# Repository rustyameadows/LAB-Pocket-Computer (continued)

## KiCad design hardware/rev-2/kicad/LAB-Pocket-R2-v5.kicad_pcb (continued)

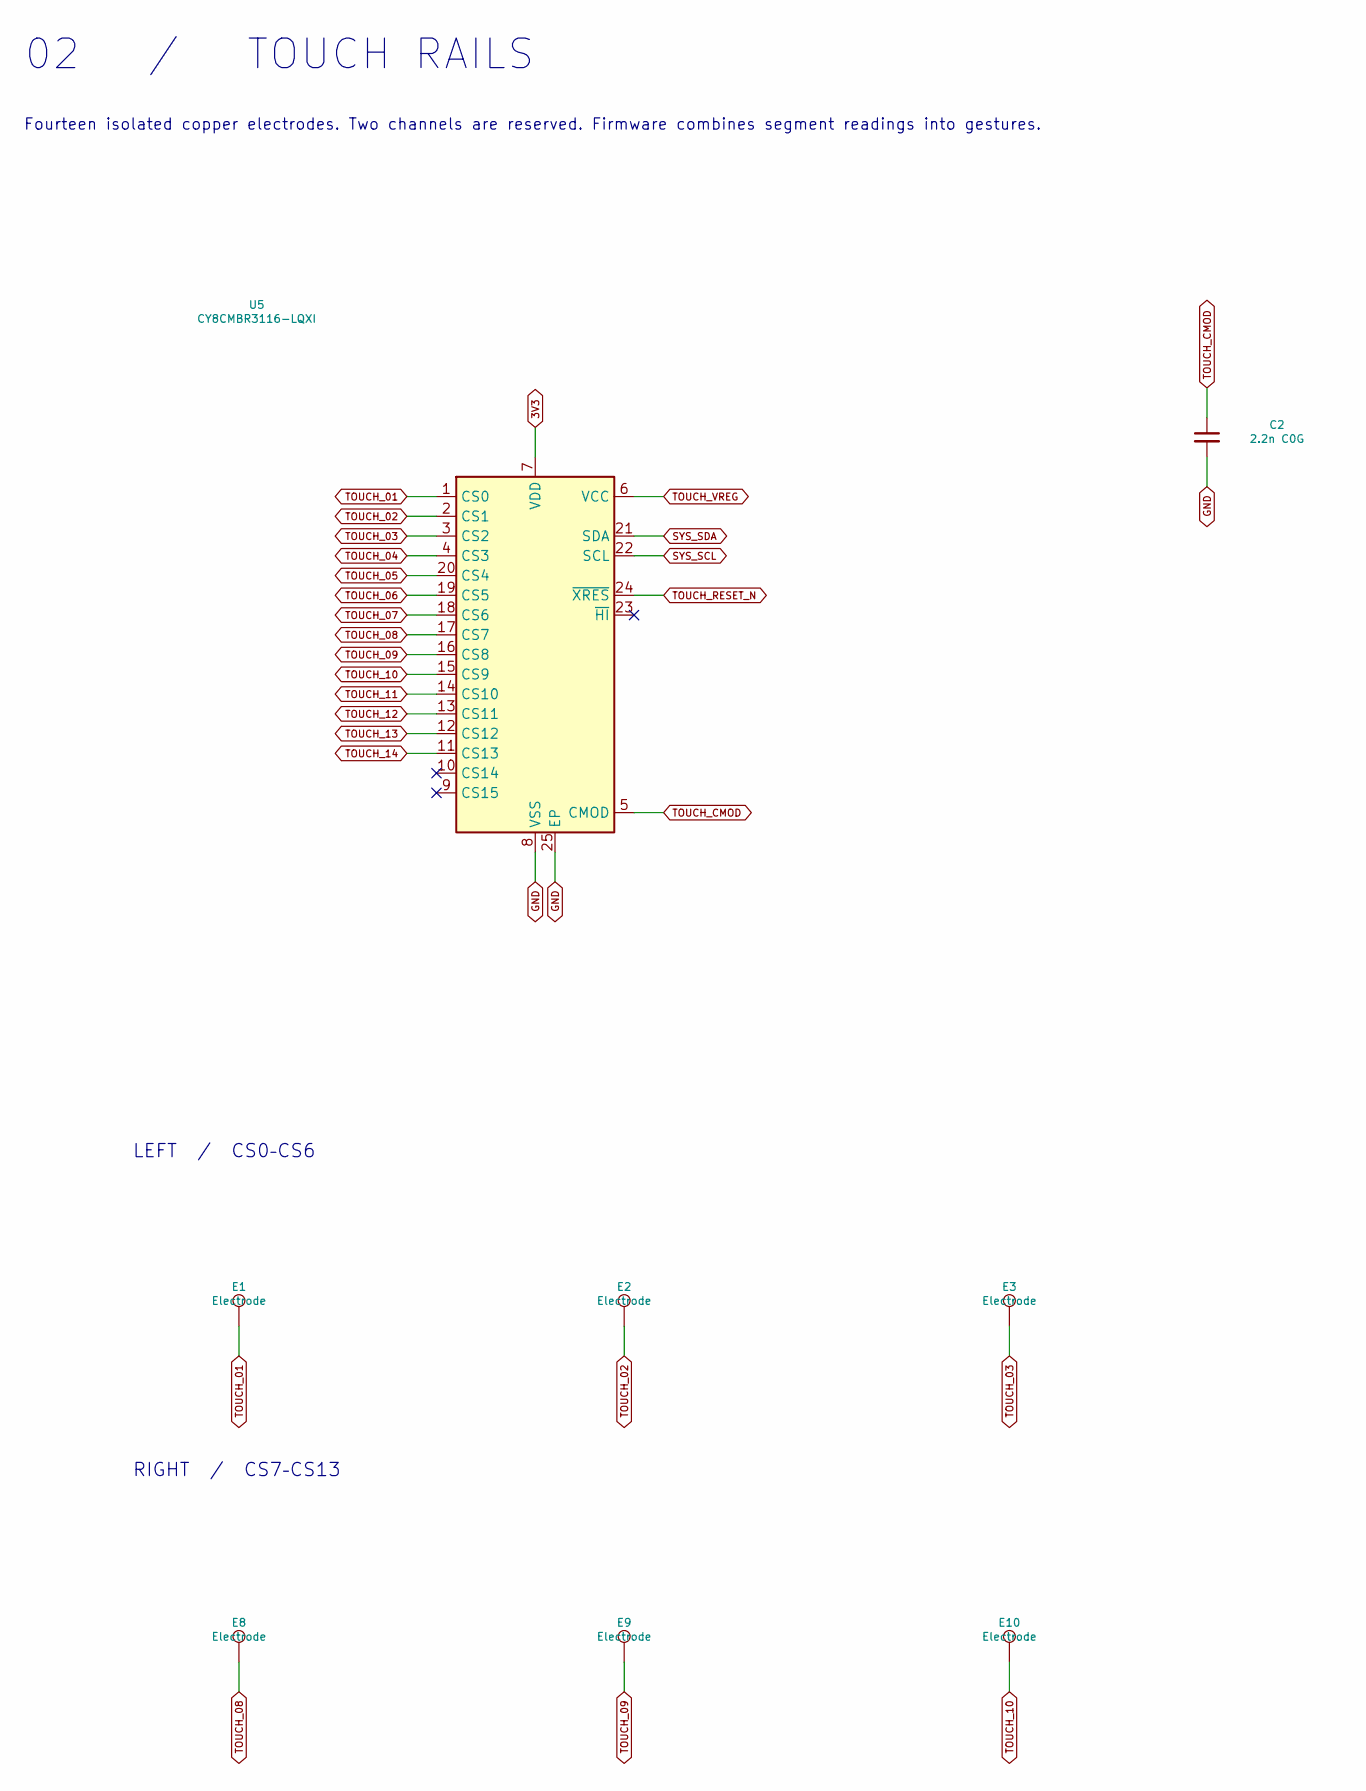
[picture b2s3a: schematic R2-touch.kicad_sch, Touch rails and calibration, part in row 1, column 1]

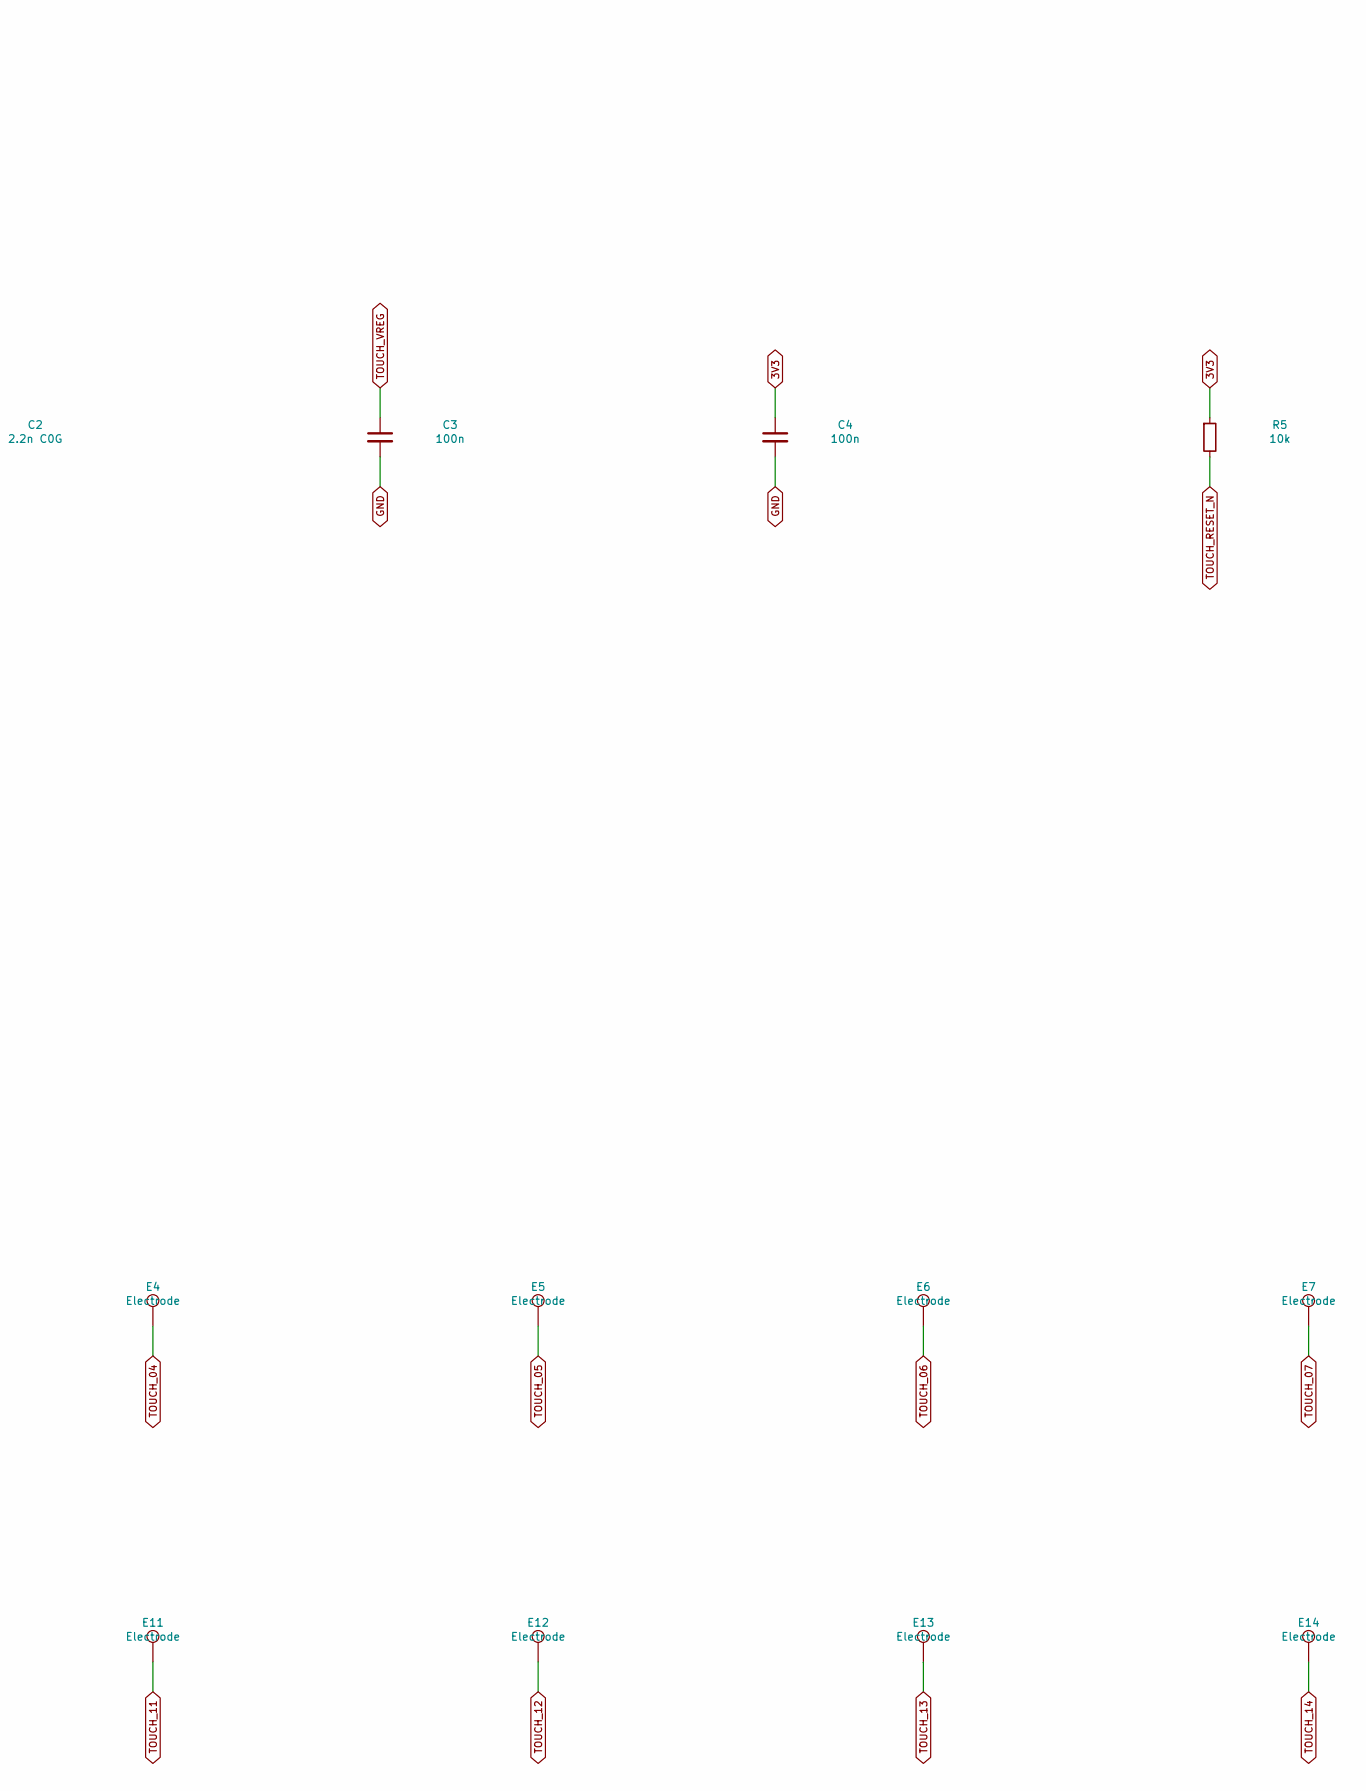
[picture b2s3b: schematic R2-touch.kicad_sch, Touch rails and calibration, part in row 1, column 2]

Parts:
C2: 2.2n C0G; C_0603_1608Metric; MPN C0603C222J5GACTU
C3, C4: 100n; C_0603_1608Metric; MPN C0603C104K5RACTU
E1, E2, E3, E4, E5, E6, E7, E8, E9, E10, E11, E12, E13, E14: Electrode; Touch_7.6x5.0; MPN PCB feature
R5: 10k; R_0603_1608Metric; MPN CRCW060310K0FKEA
U5: CY8CMBR3116-LQXI; QFN-24-1EP_4x4mm_P0.5mm_EP2.6x2.6mm; MPN CY8CMBR3116-LQXI

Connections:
3V3: C4.1, R5.1, U5.7 (VDD); also elsewhere on the board
GND: C2.2, C3.2, C4.2, U5.8 (VSS), U5.25 (EP); also elsewhere on the board
SYS_SCL: U5.22 (SCL); also elsewhere on the board
SYS_SDA: U5.21 (SDA); also elsewhere on the board
TOUCH_01: E1.1, U5.1 (CS0)
TOUCH_02: E2.1, U5.2 (CS1)
TOUCH_03: E3.1, U5.3 (CS2)
TOUCH_04: E4.1, U5.4 (CS3)
TOUCH_05: E5.1, U5.20 (CS4)
TOUCH_06: E6.1, U5.19 (CS5)
TOUCH_07: E7.1, U5.18 (CS6)
TOUCH_08: E8.1, U5.17 (CS7)
TOUCH_09: E9.1, U5.16 (CS8)
TOUCH_10: E10.1, U5.15 (CS9)
TOUCH_11: E11.1, U5.14 (CS10)
TOUCH_12: E12.1, U5.13 (CS11)
TOUCH_13: E13.1, U5.12 (CS12)
TOUCH_14: E14.1, U5.11 (CS13)
TOUCH_CMOD: C2.1, U5.5 (CMOD)
TOUCH_RESET_N: R5.2, U5.24 (~XRES)
TOUCH_VREG: C3.1, U5.6 (VCC)

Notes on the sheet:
02 / TOUCH RAILS
Fourteen isolated copper electrodes. Two channels are reserved. Firmware combines segment readings into gestures.
LEFT / CS0–CS6
RIGHT / CS7–CS13

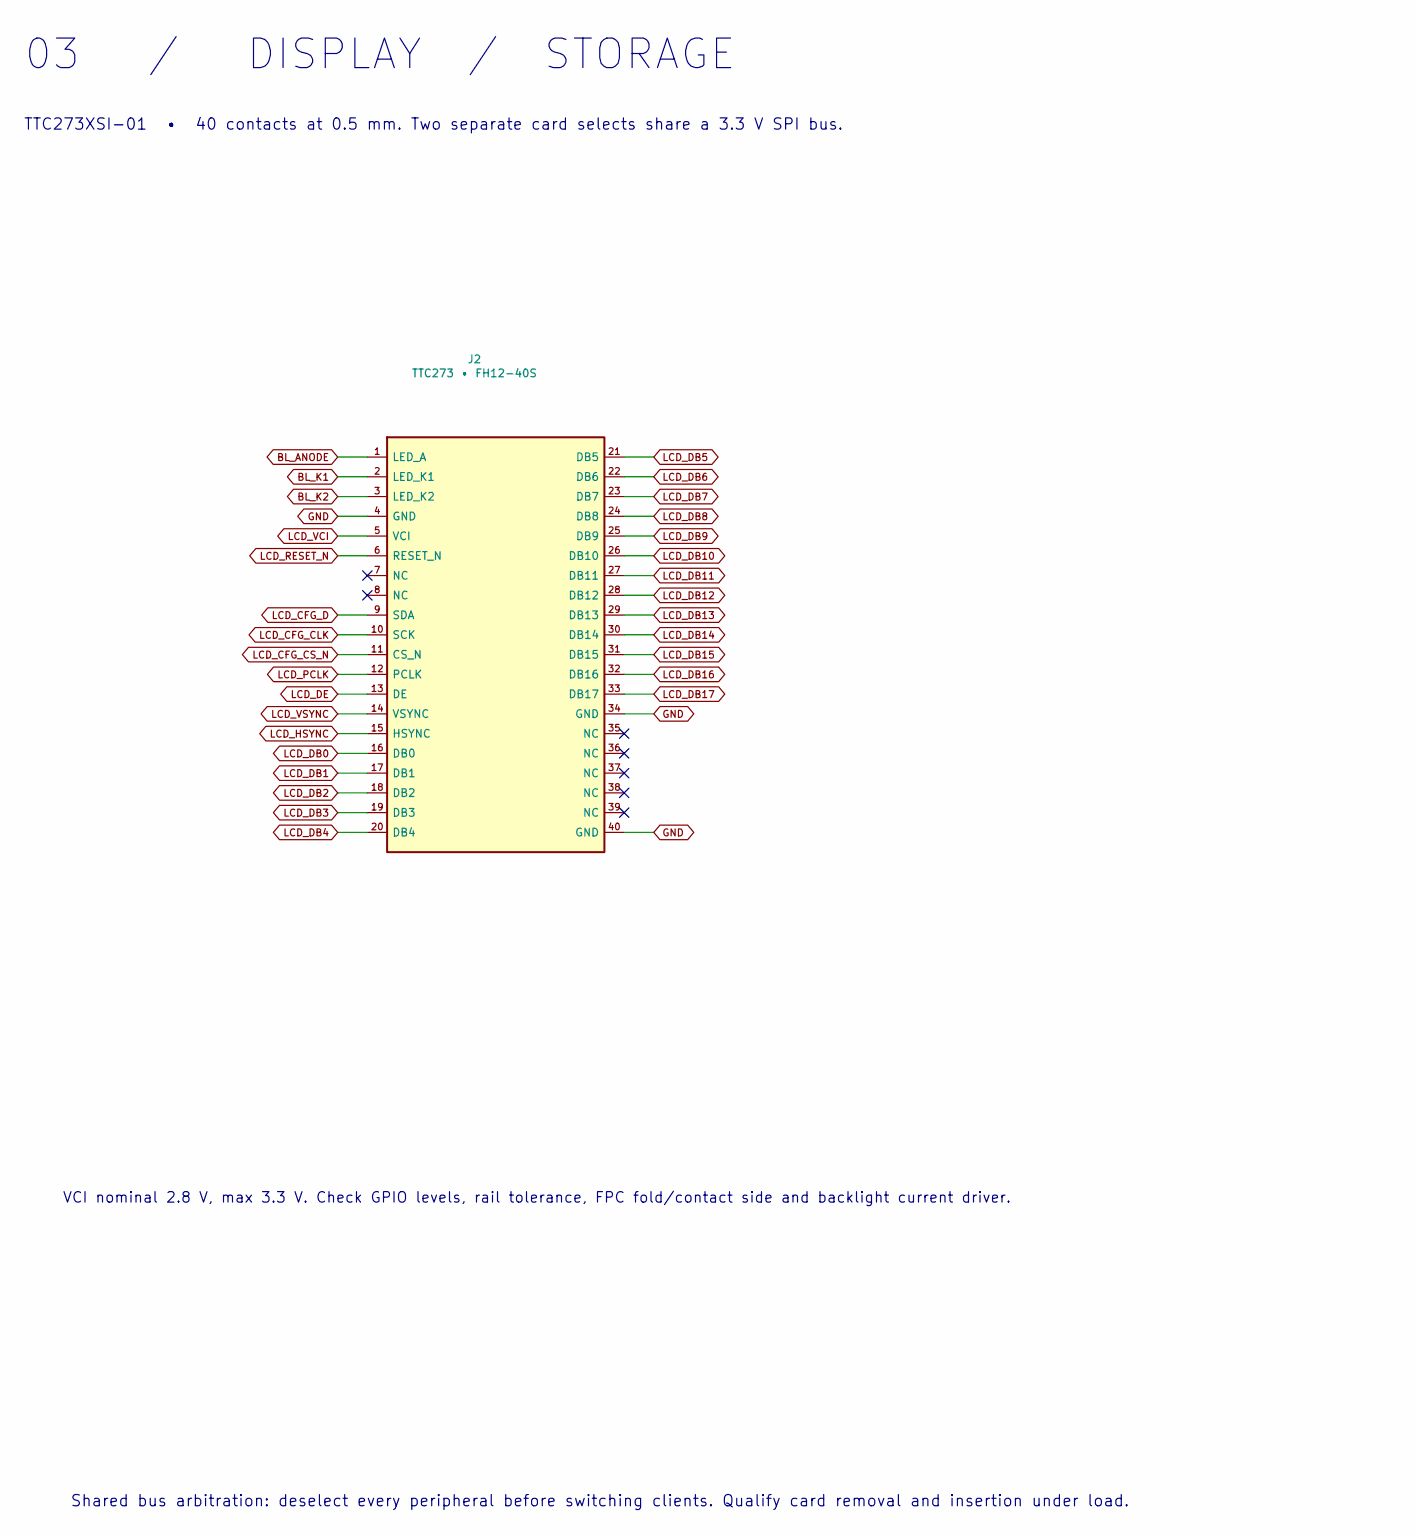
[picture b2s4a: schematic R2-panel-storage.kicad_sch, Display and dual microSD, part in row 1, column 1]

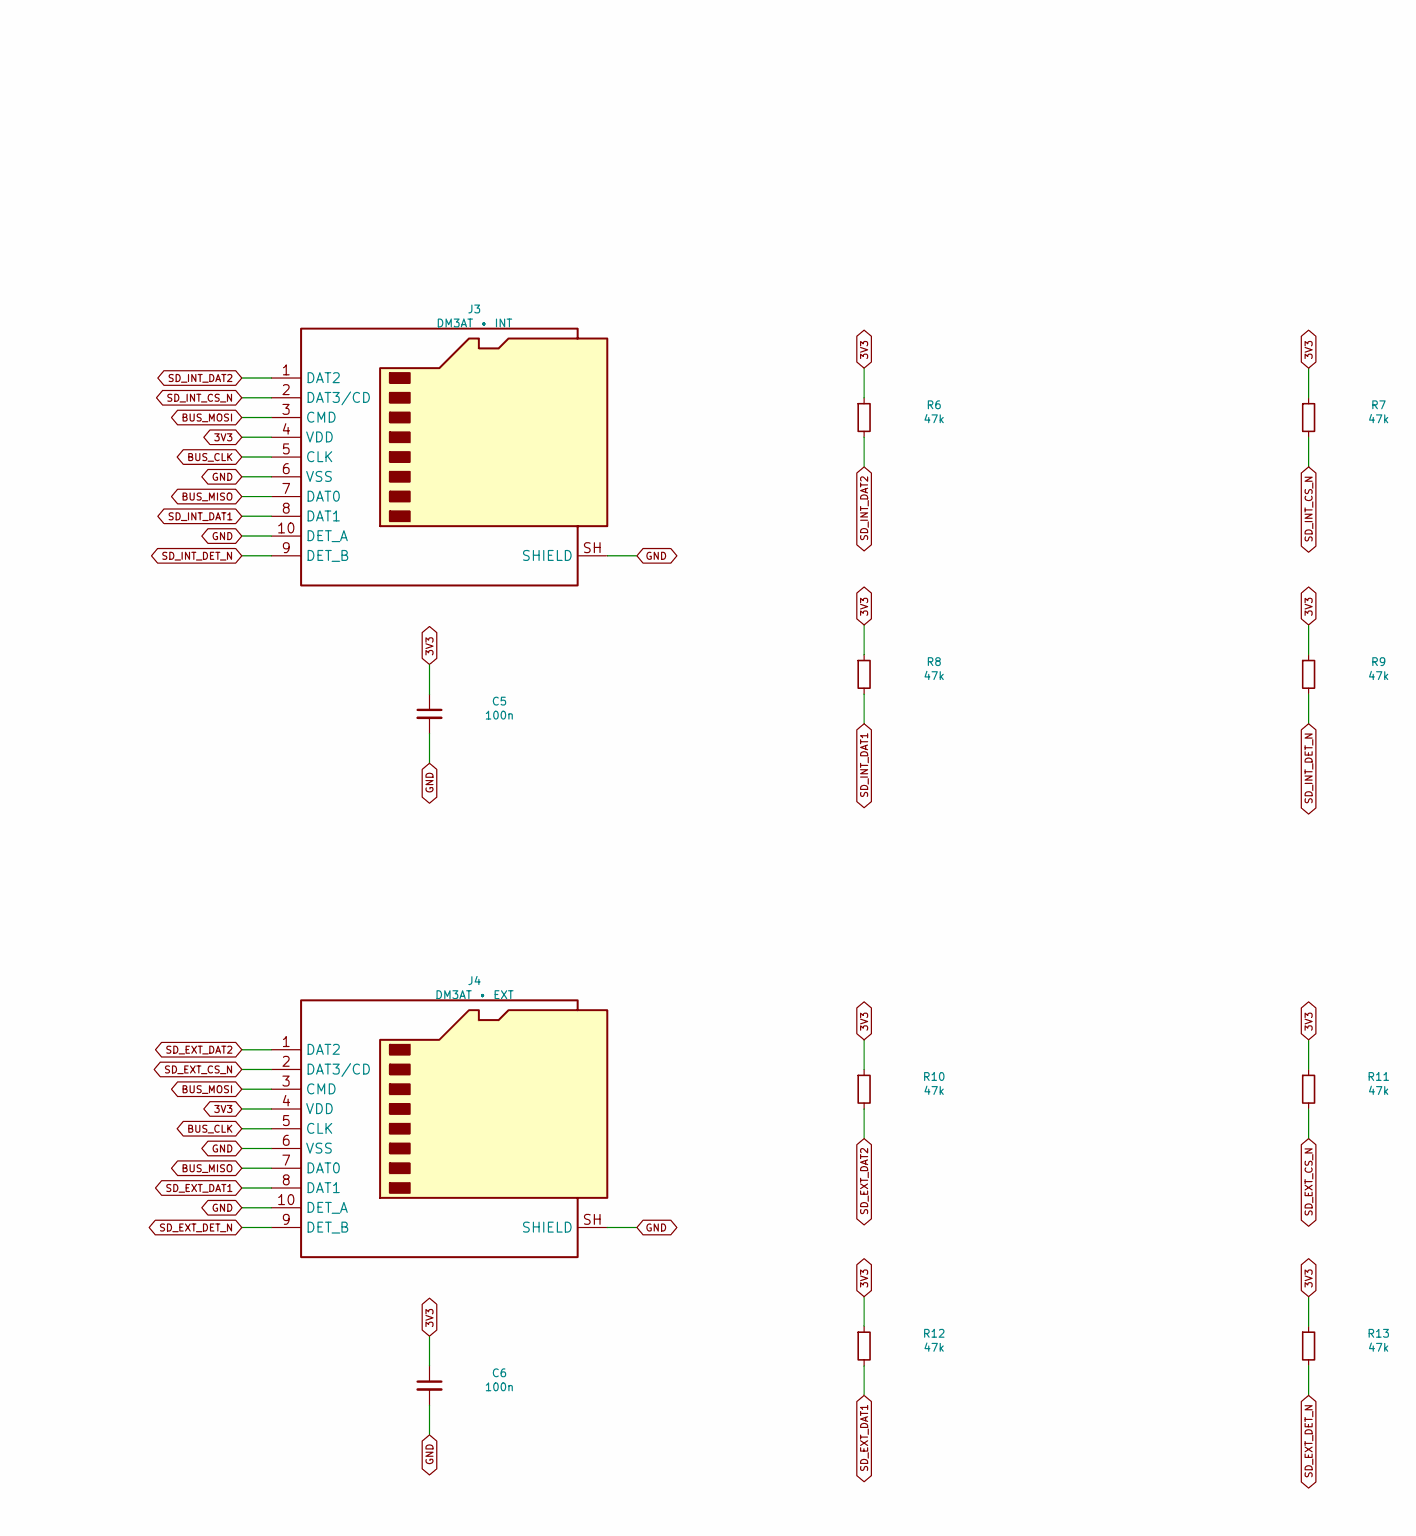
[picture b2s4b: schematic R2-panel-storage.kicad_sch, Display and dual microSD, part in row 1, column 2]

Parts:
C5, C6: 100n; C_0603_1608Metric; MPN C0603C104K5RACTU
J2: TTC273 • FH12-40S; Hirose_FH12-40S-0.5SH_1x40-1MP_P0.50mm_Horizontal; MPN FH12-40S-0.5SH(55)
J3: DM3AT • INT; microSD_HC_Hirose_DM3AT-SF-PEJM5; MPN DM3AT-SF-PEJM5
J4: DM3AT • EXT; microSD_HC_Hirose_DM3AT-SF-PEJM5; MPN DM3AT-SF-PEJM5
R6, R7, R8, R9, R10, R11, R12, R13: 47k; R_0603_1608Metric; MPN CRCW060347K0FKEA

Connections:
3V3: C5.1, C6.1, J3.4 (VDD), J4.4 (VDD), R6.1, R7.1, R8.1, R9.1, R10.1, R11.1, R12.1, R13.1; also elsewhere on the board
BL_ANODE: J2.1 (LED_A)
BL_K1: J2.2 (LED_K1)
BL_K2: J2.3 (LED_K2)
BUS_CLK: J3.5 (CLK), J4.5 (CLK); also elsewhere on the board
BUS_MISO: J3.7 (DAT0), J4.7 (DAT0); also elsewhere on the board
BUS_MOSI: J3.3 (CMD), J4.3 (CMD); also elsewhere on the board
GND: C5.2, C6.2, J2.4 (GND), J2.34 (GND), J2.40 (GND), J3.6 (VSS), J3.10 (DET_A), J3.SH (SHIELD), J4.6 (VSS), J4.10 (DET_A), J4.SH (SHIELD); also elsewhere on the board
LCD_CFG_CLK: J2.10 (SCK); also elsewhere on the board
LCD_CFG_CS_N: J2.11 (CS_N); also elsewhere on the board
LCD_CFG_D: J2.9 (SDA); also elsewhere on the board
LCD_DB0: J2.16 (DB0); also elsewhere on the board
LCD_DB1: J2.17 (DB1); also elsewhere on the board
LCD_DB2: J2.18 (DB2); also elsewhere on the board
LCD_DB3: J2.19 (DB3); also elsewhere on the board
LCD_DB4: J2.20 (DB4); also elsewhere on the board
LCD_DB5: J2.21 (DB5); also elsewhere on the board
LCD_DB6: J2.22 (DB6); also elsewhere on the board
LCD_DB7: J2.23 (DB7); also elsewhere on the board
LCD_DB8: J2.24 (DB8); also elsewhere on the board
LCD_DB9: J2.25 (DB9); also elsewhere on the board
LCD_DB10: J2.26 (DB10); also elsewhere on the board
LCD_DB11: J2.27 (DB11); also elsewhere on the board
LCD_DB12: J2.28 (DB12); also elsewhere on the board
LCD_DB13: J2.29 (DB13); also elsewhere on the board
LCD_DB14: J2.30 (DB14); also elsewhere on the board
LCD_DB15: J2.31 (DB15); also elsewhere on the board
LCD_DB16: J2.32 (DB16); also elsewhere on the board
LCD_DB17: J2.33 (DB17); also elsewhere on the board
LCD_DE: J2.13 (DE); also elsewhere on the board
LCD_HSYNC: J2.15 (HSYNC); also elsewhere on the board
LCD_PCLK: J2.12 (PCLK); also elsewhere on the board
LCD_RESET_N: J2.6 (RESET_N); also elsewhere on the board
LCD_VCI: J2.5 (VCI)
LCD_VSYNC: J2.14 (VSYNC); also elsewhere on the board
SD_EXT_CS_N: J4.2 (DAT3/CD), R11.2; also elsewhere on the board
SD_EXT_DAT1: J4.8 (DAT1), R12.2
SD_EXT_DAT2: J4.1 (DAT2), R10.2
SD_EXT_DET_N: J4.9 (DET_B), R13.2; also elsewhere on the board
SD_INT_CS_N: J3.2 (DAT3/CD), R7.2; also elsewhere on the board
SD_INT_DAT1: J3.8 (DAT1), R8.2
SD_INT_DAT2: J3.1 (DAT2), R6.2
SD_INT_DET_N: J3.9 (DET_B), R9.2; also elsewhere on the board

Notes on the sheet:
03 / DISPLAY / STORAGE
TTC273XSI-01 • 40 contacts at 0.5 mm. Two separate card selects share a 3.3 V SPI bus.
VCI nominal 2.8 V, max 3.3 V. Check GPIO levels, rail tolerance, FPC fold/contact side and backlight current driver.
Shared bus arbitration: deselect every peripheral before switching clients. Qualify card removal and insertion under load.

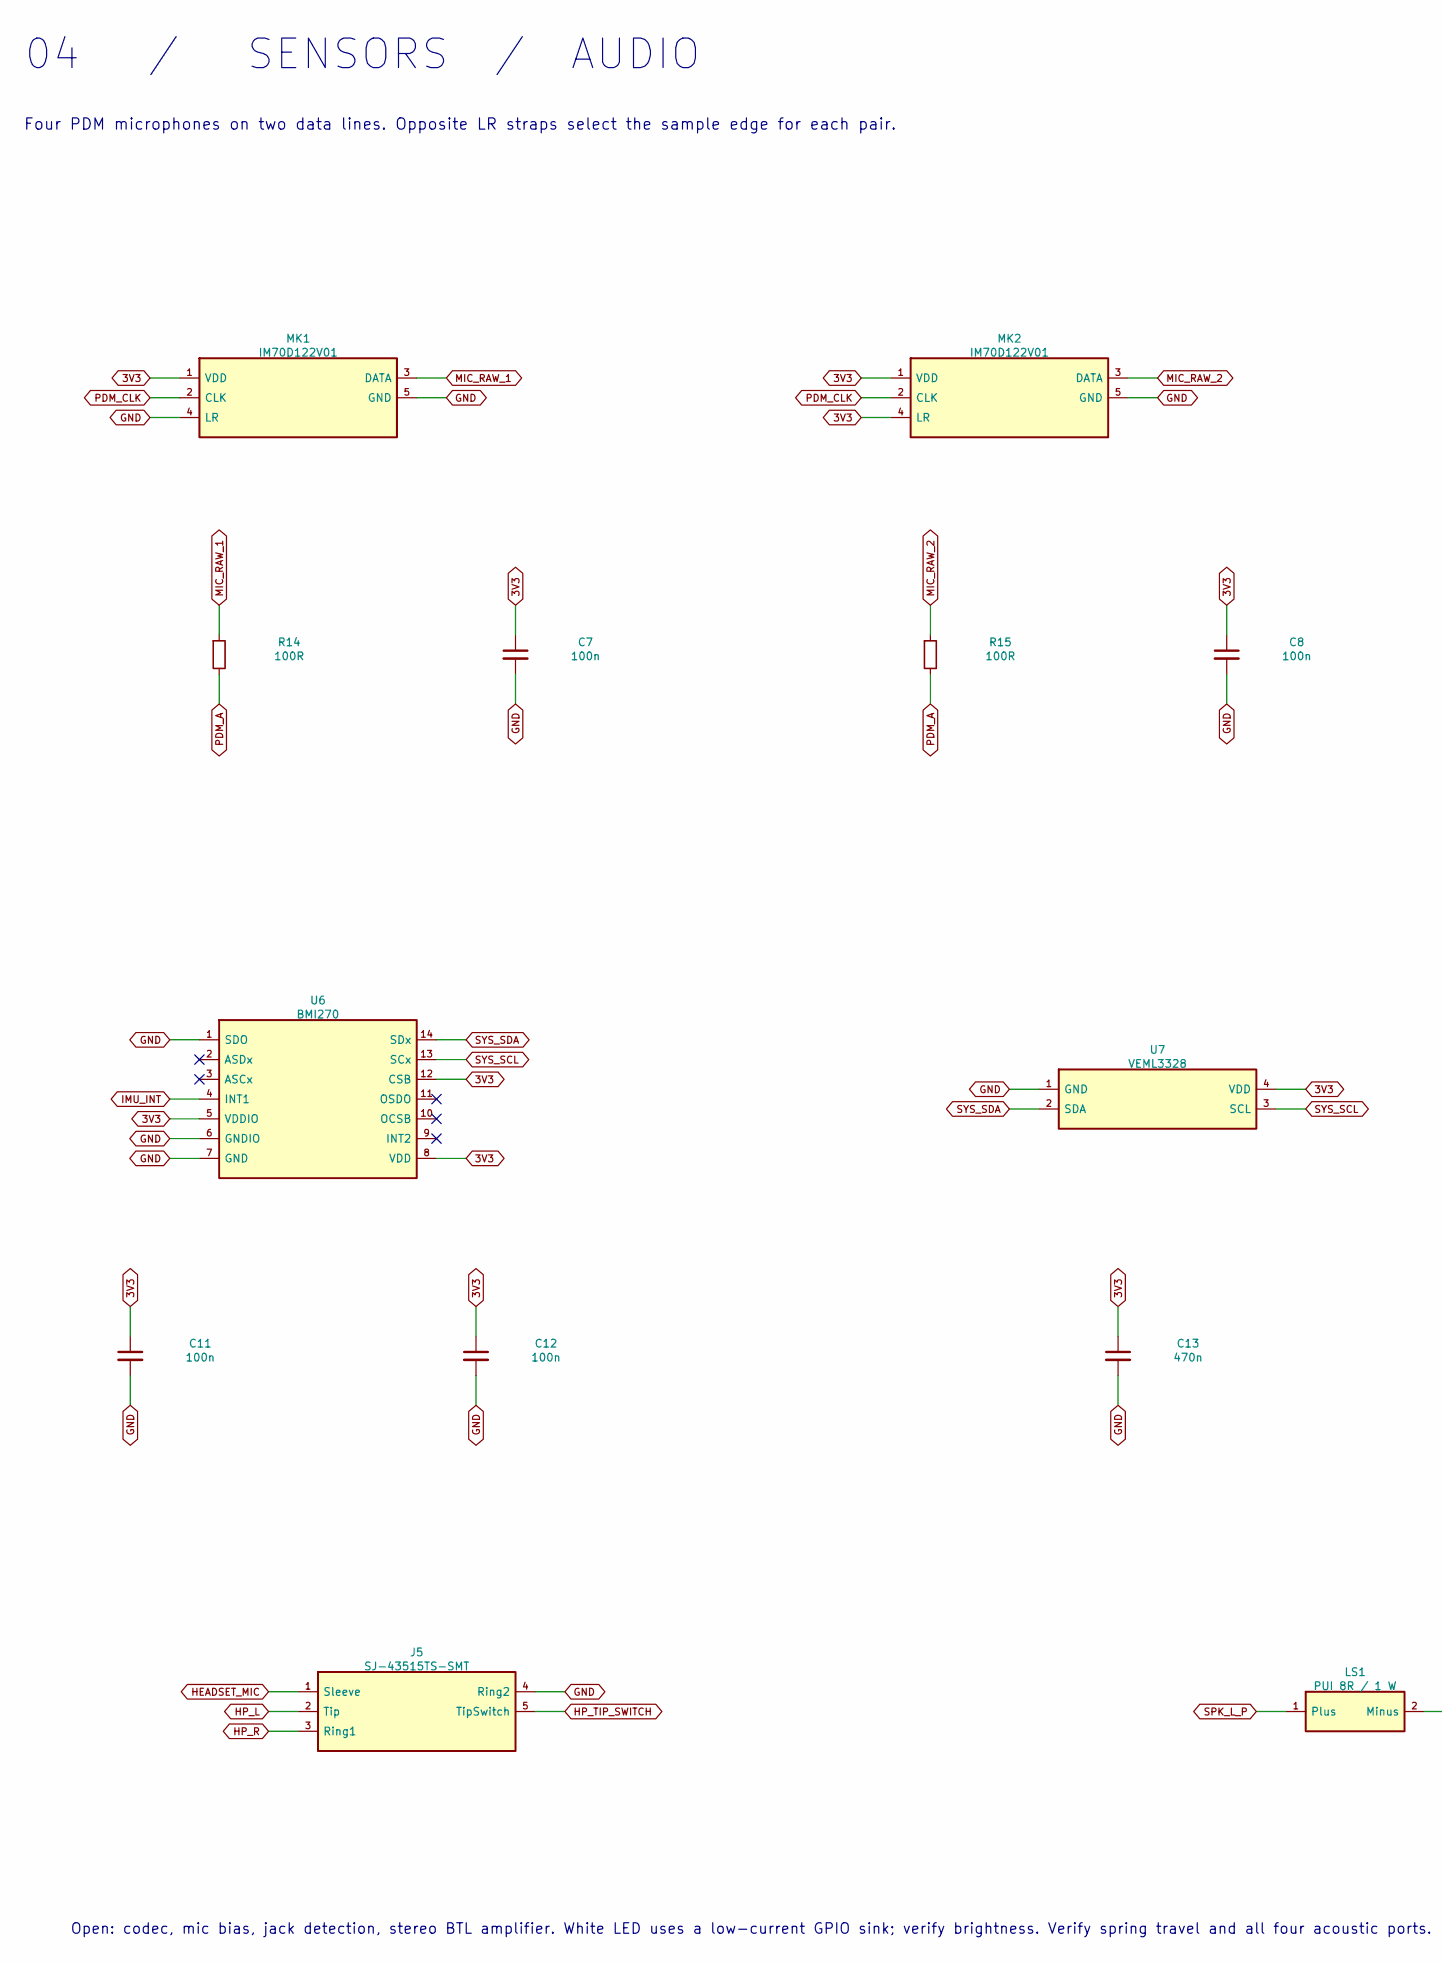
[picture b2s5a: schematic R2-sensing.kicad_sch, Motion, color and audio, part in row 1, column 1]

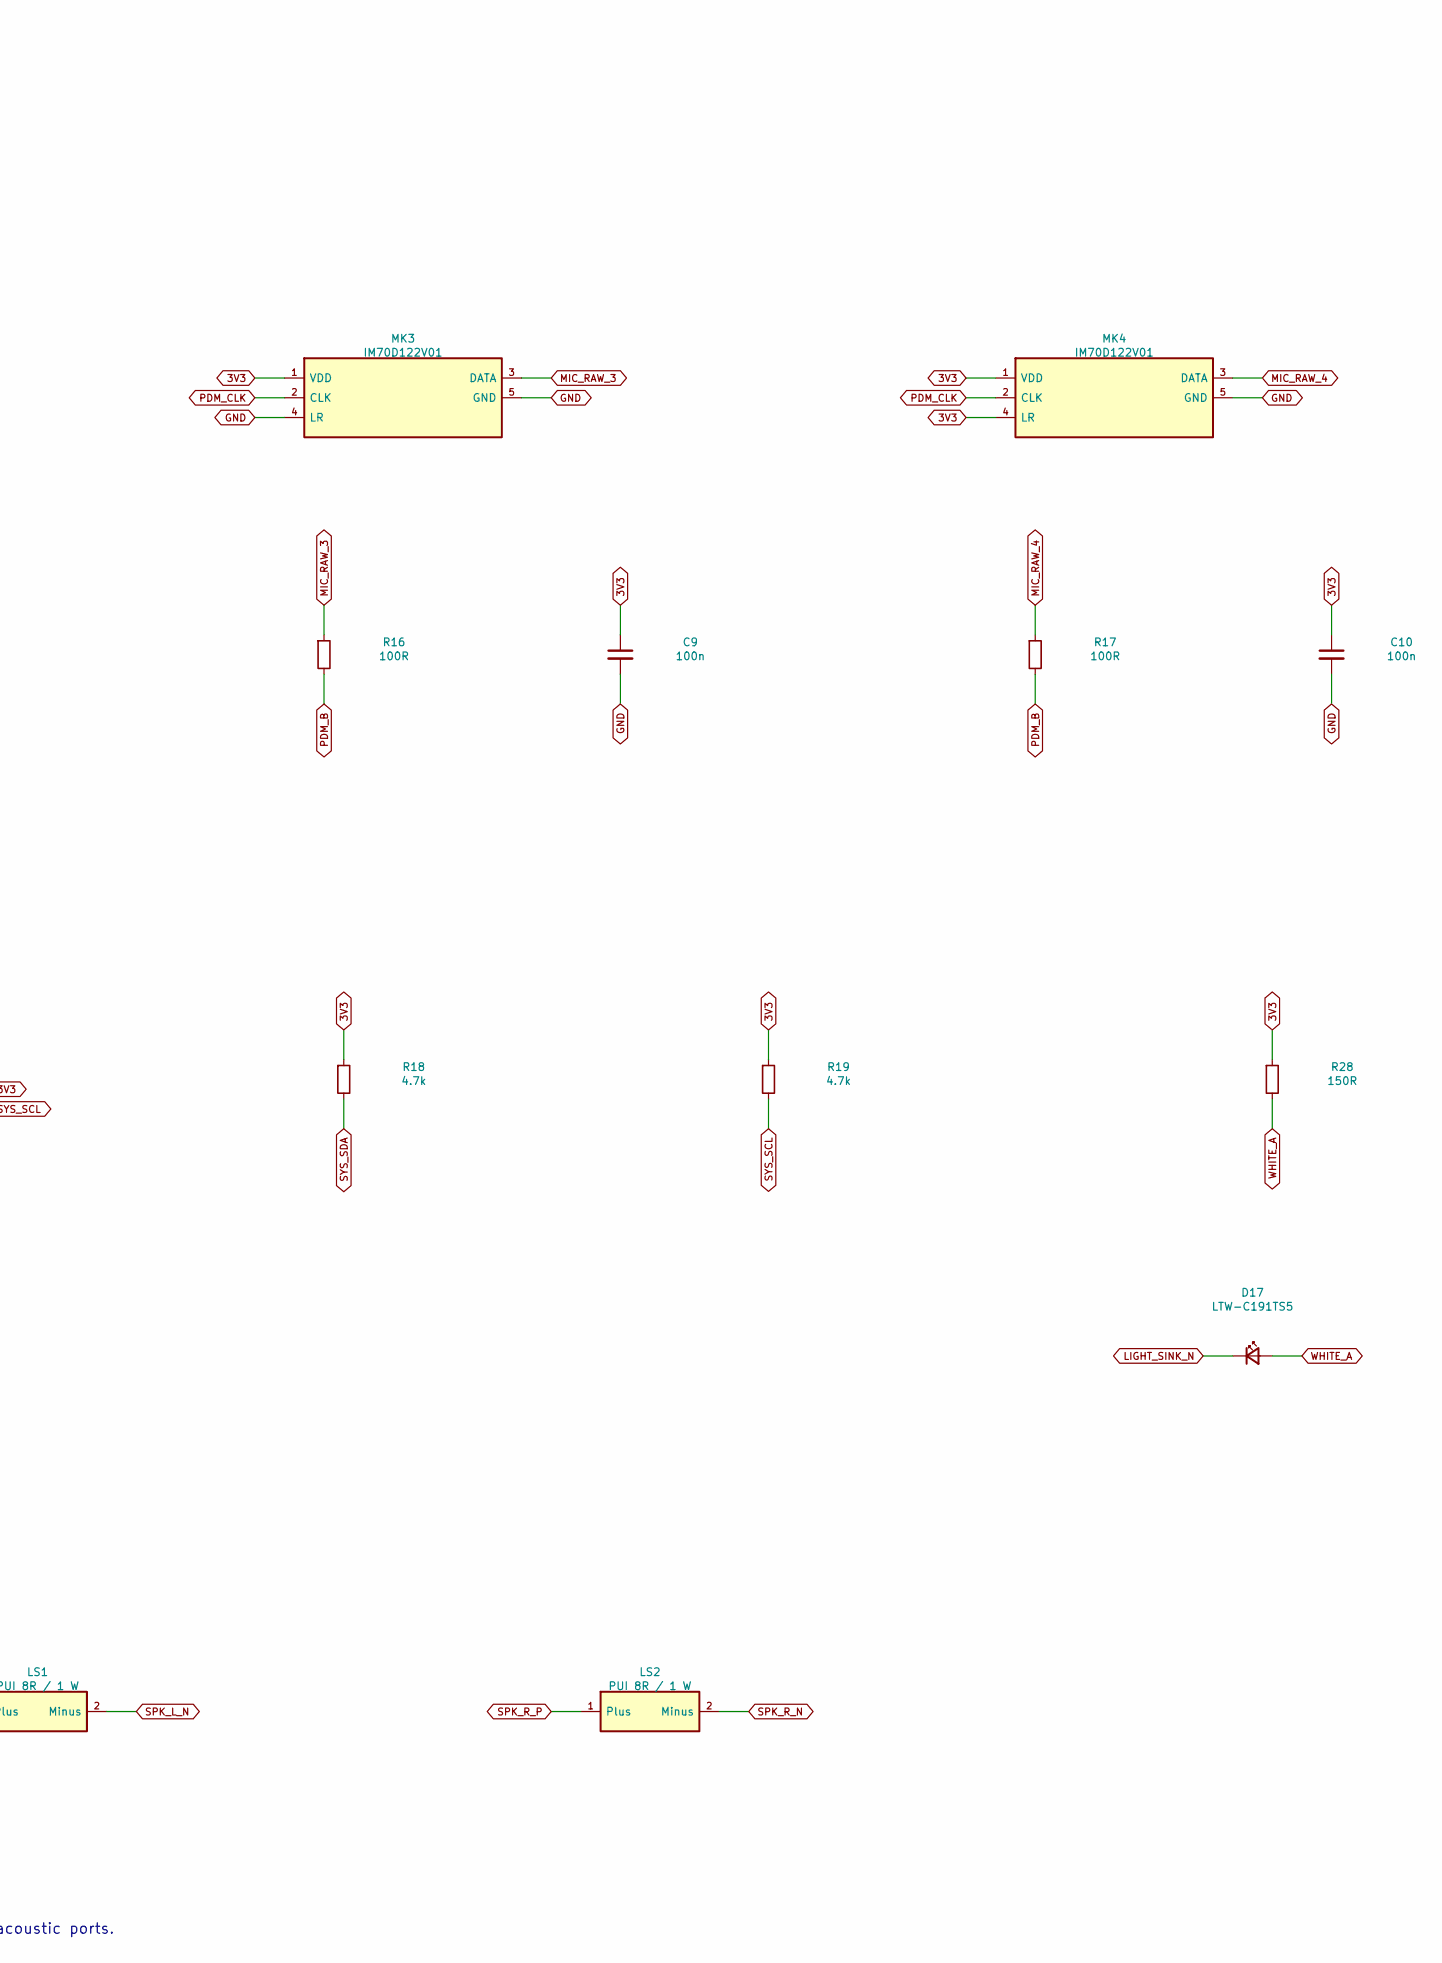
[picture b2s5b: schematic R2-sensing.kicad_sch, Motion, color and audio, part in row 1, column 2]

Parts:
C7, C8, C9, C10, C11, C12: 100n; C_0603_1608Metric; MPN C0603C104K5RACTU
C13: 470n; C_0603_1608Metric; MPN C0603C474K3RACTU
D17: LTW-C191TS5; LED_0603_1608Metric; MPN LTW-C191TS5
J5: SJ-43515TS-SMT; SJ-43515TS; MPN SJ-43515TS-SMT-TR
LS1, LS2: PUI 8R / 1 W; MPN AS01808AO-SC18-WP-R
MK1, MK2, MK3, MK4: IM70D122V01; IM70D122; MPN IM70D122V01XTMA1
R14, R15, R16, R17: 100R; R_0603_1608Metric; MPN CRCW0603100RFKEA
R18, R19: 4.7k; R_0603_1608Metric; MPN CRCW06034K70FKEA
R28: 150R; R_0603_1608Metric; MPN CRCW0603150RFKEA
U6: BMI270; Bosch_LGA-14_3x2.5mm_P0.5mm; MPN BMI270
U7: VEML3328; MPN VEML3328

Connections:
3V3: C7.1, C8.1, C9.1, C10.1, C11.1, C12.1, C13.1, MK1.1 (VDD), MK2.1 (VDD), MK2.4 (LR), MK3.1 (VDD), MK4.1 (VDD), MK4.4 (LR), R18.1, R19.1, R28.1, U6.5 (VDDIO), U6.8 (VDD), U6.12 (CSB), U7.4 (VDD); also elsewhere on the board
GND: C7.2, C8.2, C9.2, C10.2, C11.2, C12.2, C13.2, J5.4 (Ring2), MK1.4 (LR), MK1.5 (GND), MK2.5 (GND), MK3.4 (LR), MK3.5 (GND), MK4.5 (GND), U6.1 (SDO), U6.6 (GNDIO), U6.7 (GND), U7.1 (GND); also elsewhere on the board
HEADSET_MIC: J5.1 (Sleeve)
HP_L: J5.2 (Tip)
HP_R: J5.3 (Ring1)
HP_TIP_SWITCH: J5.5 (TipSwitch)
IMU_INT: U6.4 (INT1); also elsewhere on the board
LIGHT_SINK_N: D17.1 (K); also elsewhere on the board
MIC_RAW_1: MK1.3 (DATA), R14.1
MIC_RAW_2: MK2.3 (DATA), R15.1
MIC_RAW_3: MK3.3 (DATA), R16.1
MIC_RAW_4: MK4.3 (DATA), R17.1
PDM_A: R14.2, R15.2; also elsewhere on the board
PDM_B: R16.2, R17.2; also elsewhere on the board
PDM_CLK: MK1.2 (CLK), MK2.2 (CLK), MK3.2 (CLK), MK4.2 (CLK); also elsewhere on the board
SYS_SCL: R19.2, U6.13 (SCx), U7.3 (SCL); also elsewhere on the board
SYS_SDA: R18.2, U6.14 (SDx), U7.2 (SDA); also elsewhere on the board
WHITE_A: D17.2 (A), R28.2

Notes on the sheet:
04 / SENSORS / AUDIO
Four PDM microphones on two data lines. Opposite LR straps select the sample edge for each pair.
Open: codec, mic bias, jack detection, stereo BTL amplifier. White LED uses a low-current GPIO sink; verify brightness. Verify spring travel and all four acoustic ports.
